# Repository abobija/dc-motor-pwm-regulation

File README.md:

# dc-motor-pwm-regulation
DC Motor PWM speed regulation and IR tachometer

## Description

One MCU is responsible for regulation speed of DC motor with Pulse Width Modulation (PWM), while other MCU have responsibility for measuring that speed. Everything will be easy if there is wire connection between this two MCUs, but there are no physical connection between them. CD which contains four drilled holes, rotates between IR emitting diode, and phototransistor on opposite side. When the hole drilled on CD comes to the sensor, and IR light pass from diode to transistor, internal MCU interrupt will be triggered. Applications for both MCUs are written in plain C.

## Demo

## Microcontrollers

- PWM Generator - `PIC12F628`
- Tachometer - `PIC16F886`

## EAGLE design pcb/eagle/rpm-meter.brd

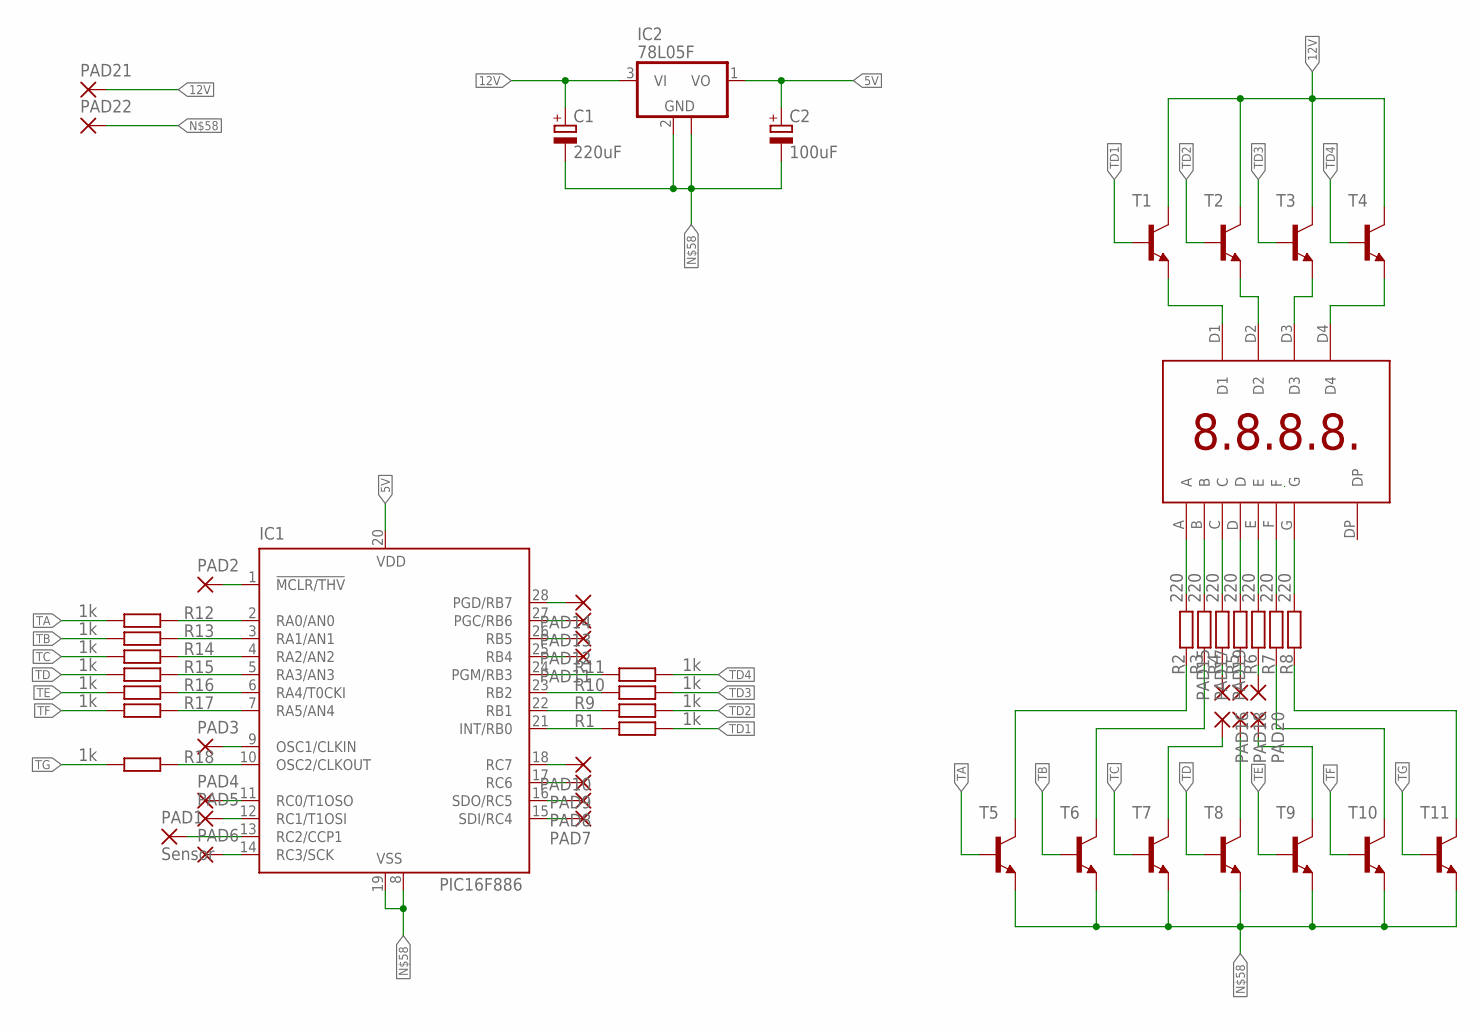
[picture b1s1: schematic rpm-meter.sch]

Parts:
C1: 220uF; E5-6
C2: 100uF; E5-5
IC1: PIC16F886; DIL28-3
IC2: 78L05F; SOT89
PAD1: Sensor; SMD2,54-5,08
PAD2, PAD3, PAD4, PAD5, PAD6, PAD7, PAD8, PAD9, PAD10, PAD11, PAD12, PAD13, PAD14: SMD2; SMD1,27-2,54
PAD15, PAD16, PAD17, PAD18, PAD19, PAD20: 2,54/0,8
PAD21, PAD22: SMD5; SMD2,54-5,08
R1, R9, R10, R11, R12, R13, R14, R15, R16, R17, R18: 1k; M0805
R2, R3, R4, R5, R6, R7, R8: 220; M0805
T1, T2, T3, T4, T5, T6, T7, T8, T9, T10, T11: -NPN-SOT23-EBC; SOT23-EBC
U$1: 4X7SEG-CA

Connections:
5V: C2.+, IC1.20 (VDD), IC2.1 (VO)
12V: C1.+, IC2.3 (VI), PAD21.1, T1.C, T2.C, T3.C, T4.C
unnamed: R2.2, U$1.A
unnamed: R3.2, U$1.B
unnamed: R4.2, U$1.C
unnamed: R5.2, U$1.D
unnamed: R6.2, U$1.E
unnamed: R7.2, U$1.F
unnamed: R8.2, U$1.G
unnamed: T2.E, U$1.D2
unnamed: T3.E, U$1.D3
unnamed: T1.E, U$1.D1
unnamed: T4.E, U$1.D4
unnamed: PAD17.1, R5.1
unnamed: PAD20.1, T9.C
unnamed: R7.1, T10.C
unnamed: R8.1, T11.C
unnamed: PAD16.1, T7.C
unnamed: R3.1, T6.C
unnamed: R2.1, T5.C
unnamed: IC1.21 (INT/RB0), R1.1
unnamed: IC1.22 (RB1), R9.1
unnamed: IC1.23 (RB2), R10.1
unnamed: IC1.24 (PGM/RB3), R11.1
unnamed: IC1.2 (RA0/AN0), R12.1
unnamed: IC1.3 (RA1/AN1), R13.1
unnamed: IC1.4 (RA2/AN2), R14.1
unnamed: IC1.5 (RA3/AN3), R15.1
unnamed: IC1.6 (RA4/T0CKI), R16.1
unnamed: IC1.7 (RA5/AN4), R17.1
unnamed: IC1.10 (OSC2/CLKOUT), R18.1
unnamed: IC1.13 (RC2/CCP1), PAD1.1
unnamed: IC1.1 (!MCLR/THV), PAD2.1
unnamed: IC1.9 (OSC1/CLKIN), PAD3.1
unnamed: IC1.11 (RC0/T1OSO), PAD4.1
unnamed: IC1.12 (RC1/T1OSI), PAD5.1
unnamed: IC1.14 (RC3/SCK), PAD6.1
unnamed: IC1.15 (SDI/RC4), PAD7.1
unnamed: IC1.16 (SDO/RC5), PAD8.1
unnamed: IC1.17 (RC6), PAD9.1
unnamed: IC1.18 (RC7), PAD10.1
unnamed: IC1.25 (RB4), PAD11.1
unnamed: IC1.26 (RB5), PAD12.1
unnamed: IC1.27 (PGC/RB6), PAD13.1
unnamed: IC1.28 (PGD/RB7), PAD14.1
unnamed: PAD15.1, R4.1
unnamed: PAD19.1, R6.1
unnamed: PAD18.1, T8.C
unnamed: C1.-, C2.-, IC1.8 (VSS), IC1.19 (VSS), IC2.2 (GND), IC2.2@1 (GND), PAD22.1, T5.E, T6.E, T7.E, T8.E, T9.E, T10.E, T11.E
TA: R12.2, T5.B
TB: R13.2, T6.B
TC: R14.2, T7.B
TD: R15.2, T8.B
TD1: R1.2, T1.B
TD2: R9.2, T2.B
TD3: R10.2, T3.B
TD4: R11.2, T4.B
TE: R16.2, T9.B
TF: R17.2, T10.B
TG: R18.2, T11.B

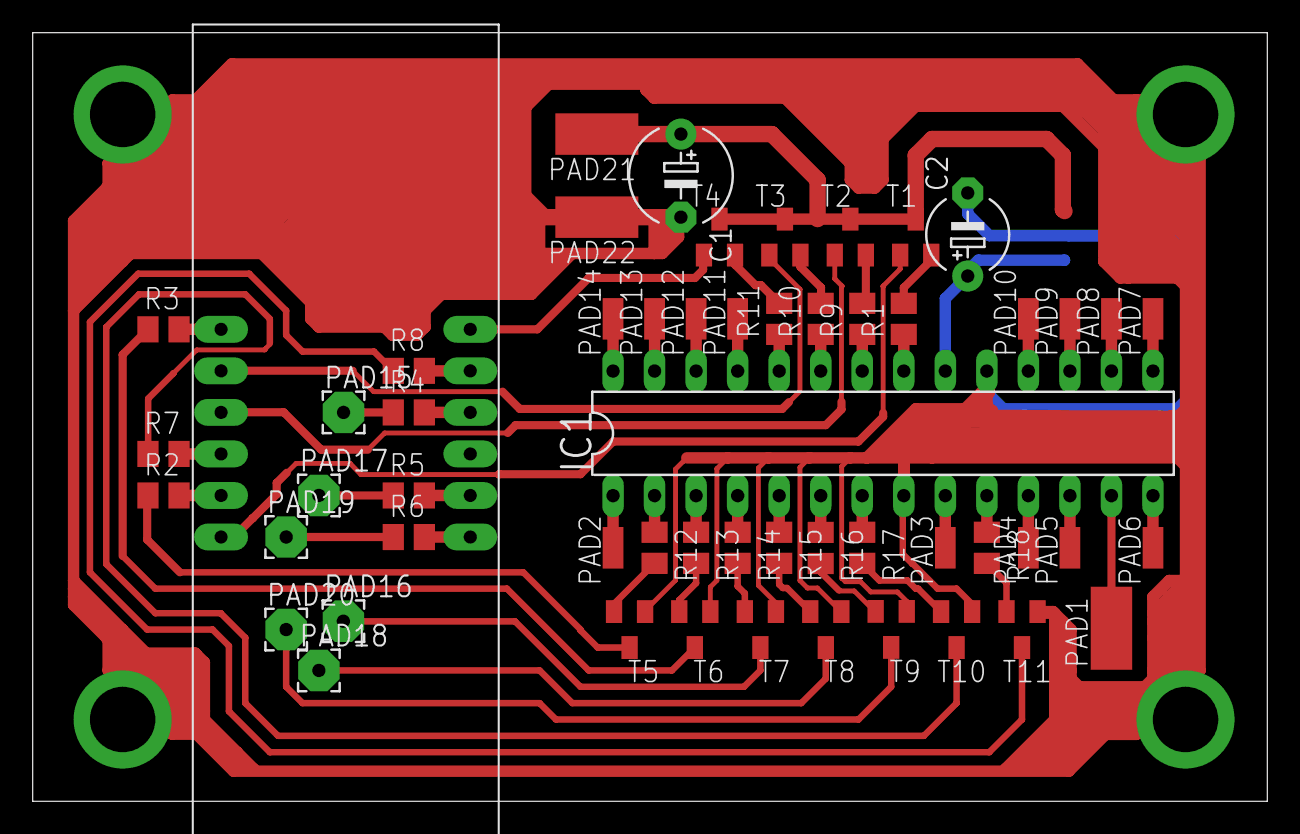
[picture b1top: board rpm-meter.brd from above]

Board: 2 copper layers, 75.5 x 47.0 mm, 56 parts (1 on the bottom side), 60 nets.

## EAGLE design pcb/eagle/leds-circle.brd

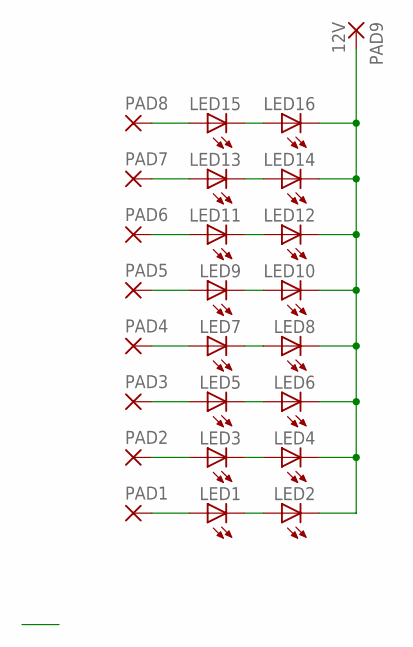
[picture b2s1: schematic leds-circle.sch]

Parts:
LED1, LED2, LED3, LED4, LED5, LED6, LED7, LED8, LED9, LED10, LED11, LED12, LED13, LED14, LED15, LED16: LED-FKIT-1206; FKIT-LED-1206
PAD1, PAD2, PAD3, PAD4, PAD5, PAD6, PAD7, PAD8: SMD2; SMD1,27-2,54
PAD9: 12V; SMD1,27-2,54

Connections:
unnamed: LED1.C, LED2.A
unnamed: LED3.C, LED4.A
unnamed: LED5.C, LED6.A
unnamed: LED7.C, LED8.A
unnamed: LED9.C, LED10.A
unnamed: LED11.C, LED12.A
unnamed: LED13.C, LED14.A
unnamed: LED15.C, LED16.A
unnamed: LED15.A, PAD8.1
unnamed: LED13.A, PAD7.1
unnamed: LED11.A, PAD6.1
unnamed: LED7.A, PAD4.1
unnamed: LED5.A, PAD3.1
unnamed: LED3.A, PAD2.1
unnamed: LED1.A, PAD1.1
unnamed: LED2.C, LED4.C, LED6.C, LED8.C, LED10.C, LED12.C, LED14.C, LED16.C, PAD9.1
unnamed: LED9.A, PAD5.1

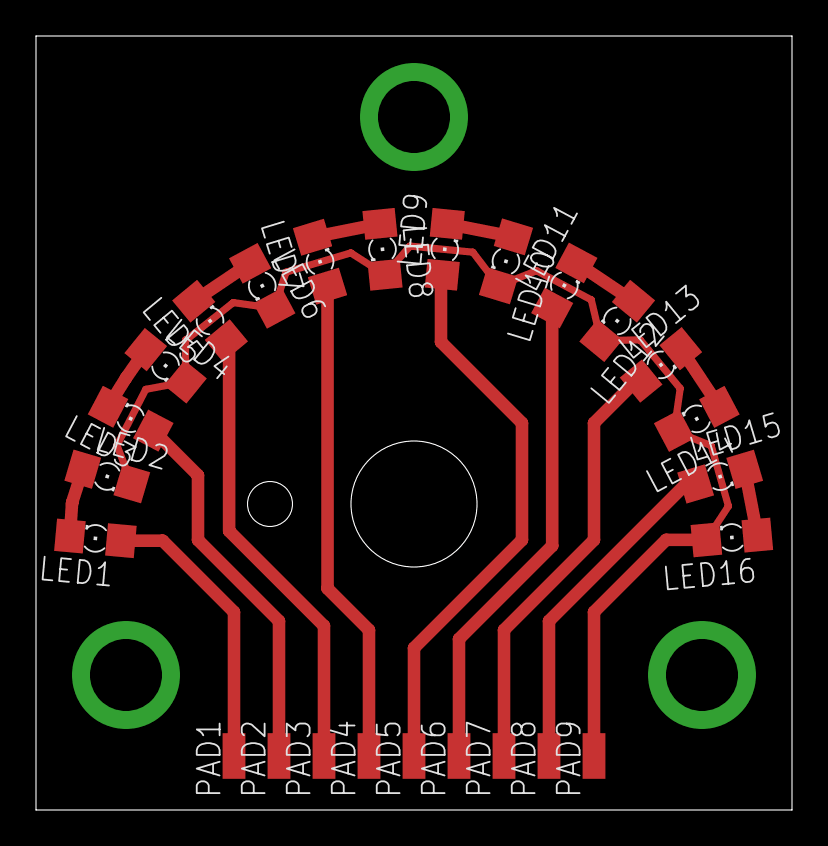
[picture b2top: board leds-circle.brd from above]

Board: 2 copper layers, 42.0 x 43.0 mm, 25 parts (0 on the bottom side), 17 nets.

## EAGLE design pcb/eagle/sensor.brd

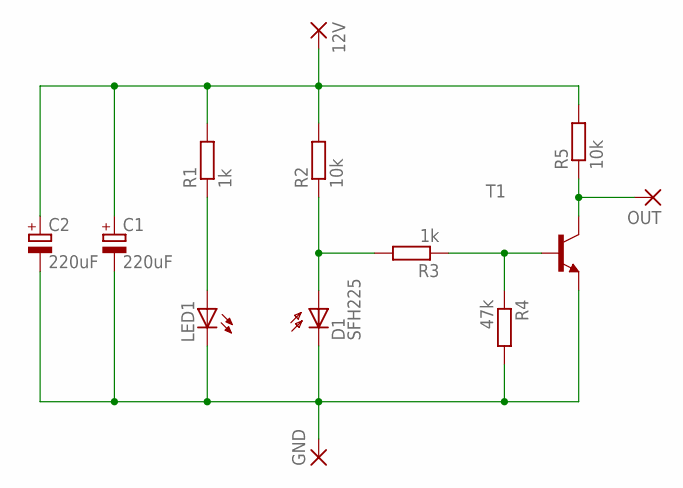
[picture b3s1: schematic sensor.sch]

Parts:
12V: SMD2; SMD1,27-2,54
C1, C2: 220uF; E5-6
D1: SFH225
GND: SMD2; SMD1,27-2,54
LED1: LED3MM
OUT: SMD2; SMD1,27-2,54
R1, R3: 1k; M0805
R2, R5: 10k; M0805
R4: 47k; M0805
T1: -NPN-SOT23-EBC; SOT23-EBC

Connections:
unnamed: C1.-, C2.-, D1.K (C), GND.1, LED1.K (C), R4.2, T1.E
unnamed: D1.A, R2.1, R3.2
unnamed: LED1.A, R1.1
unnamed: 12V.1, C1.+, C2.+, R1.2, R2.2, R5.2
unnamed: R3.1, R4.1, T1.B
unnamed: OUT.1, R5.1, T1.C

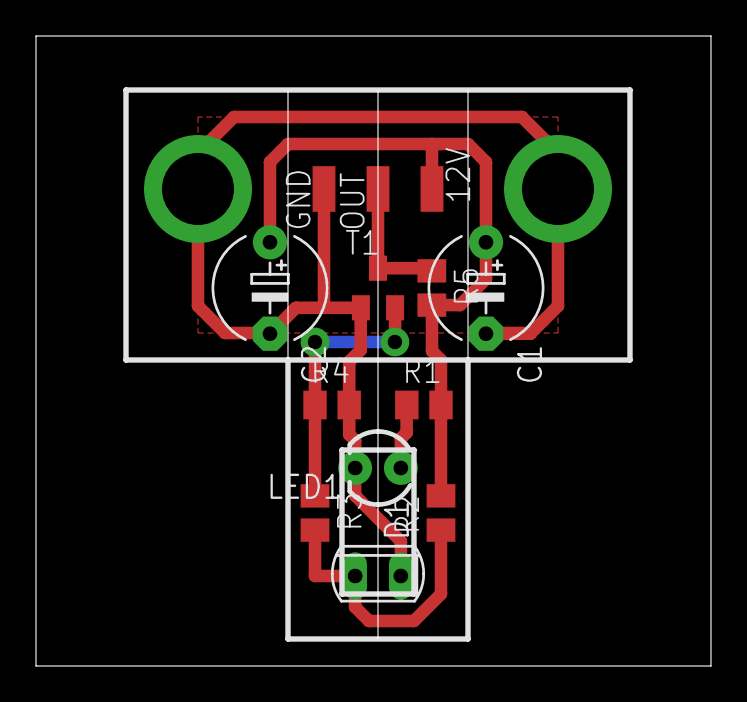
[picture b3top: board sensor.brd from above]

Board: 2 copper layers, 37.5 x 35.0 mm, 13 parts (0 on the bottom side), 6 nets.

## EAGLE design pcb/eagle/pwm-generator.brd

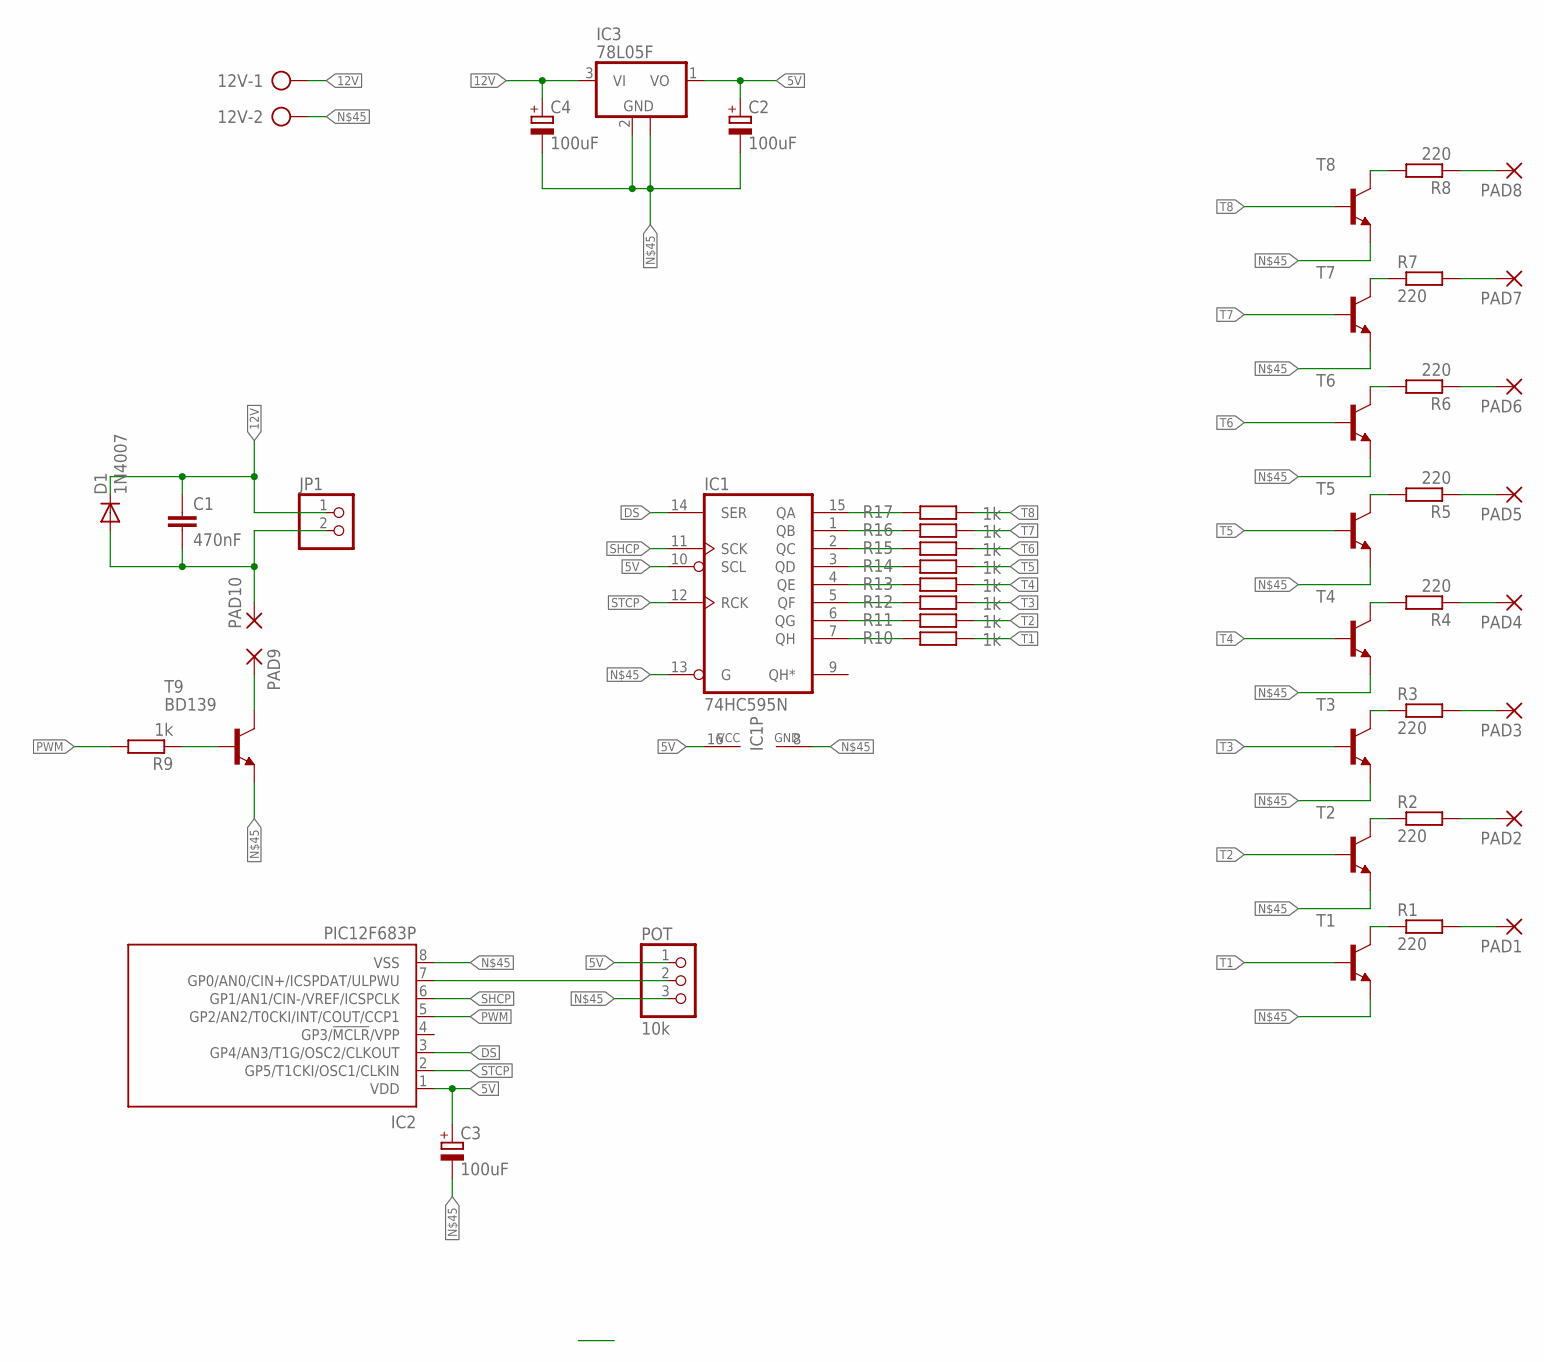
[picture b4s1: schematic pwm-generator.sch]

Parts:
12V: AK500/2
C1: 470nF; C025-025X050
C2, C4: 100uF; E2-5
C3: 100uF; E5-4
D1: 1N4007; DO35-7
IC1: 74HC595N; DIL16
IC2: PIC12F683P; DIL8
IC3: 78L05F; SOT89
JP1: PINHD-1X2; 1X02
PAD1, PAD2, PAD3, PAD4, PAD5, PAD6, PAD7, PAD8: SMD2; SMD1,27-2,54
PAD9, PAD10: 1,6/0,8
POT: 10k; 1X03
R1, R2, R3, R4, R5, R6, R7, R8: 220; M0805
R9, R10, R11, R12, R13, R14, R15, R16, R17: 1k; M0805
T1, T2, T3, T4, T5, T6, T7, T8: -NPN-SOT23-EBC; SOT23-EBC
T9: BD139; TO126

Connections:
5V: C2.+, C3.+, IC1.10 (SCL), IC1.16 (VCC), IC2.1 (VDD), IC3.1 (VO), POT.1
12V: 12V.1, C1.1, C4.+, D1.C, IC3.3 (VI), JP1.1
DS: IC1.14 (SER), IC2.3 (GP4/AN3/T1G/OSC2/CLKOUT)
unnamed: IC1.7 (QH), R10.2
unnamed: IC1.6 (QG), R11.2
unnamed: IC1.5 (QF), R12.2
unnamed: IC1.4 (QE), R13.2
unnamed: IC1.3 (QD), R14.2
unnamed: IC1.2 (QC), R15.2
unnamed: IC1.1 (QB), R16.2
unnamed: IC1.15 (QA), R17.2
unnamed: IC2.7 (GP0/AN0/CIN+/ICSPDAT/ULPWU), POT.2
unnamed: C1.2, D1.A, JP1.2, PAD10.1
unnamed: R9.1, T9.3 (B)
unnamed: R1.1, T1.C
unnamed: R2.1, T2.C
unnamed: R3.1, T3.C
unnamed: R4.2, T4.C
unnamed: R5.2, T5.C
unnamed: R6.2, T6.C
unnamed: R7.1, T7.C
unnamed: R8.2, T8.C
unnamed: PAD8.1, R8.1
unnamed: PAD7.1, R7.2
unnamed: PAD6.1, R6.1
unnamed: PAD5.1, R5.1
unnamed: PAD4.1, R4.1
unnamed: PAD3.1, R3.2
unnamed: PAD2.1, R2.2
unnamed: PAD1.1, R1.2
unnamed: PAD9.1, T9.2 (C)
unnamed: 12V.2, C2.-, C3.-, C4.-, IC1.8 (GND), IC1.13 (G), IC2.8 (VSS), IC3.2 (GND), IC3.2@1 (GND), POT.3, T1.E, T2.E, T3.E, T4.E, T5.E, T6.E, T7.E, T8.E, T9.1 (E)
PWM: IC2.5 (GP2/AN2/T0CKI/INT/COUT/CCP1), R9.2
SHCP: IC1.11 (SCK), IC2.6 (GP1/AN1/CIN-/VREF/ICSPCLK)
STCP: IC1.12 (RCK), IC2.2 (GP5/T1CKI/OSC1/CLKIN)
T1: R10.1, T1.B
T2: R11.1, T2.B
T3: R12.1, T3.B
T4: R13.1, T4.B
T5: R14.1, T5.B
T6: R15.1, T6.B
T7: R16.1, T7.B
T8: R17.1, T8.B

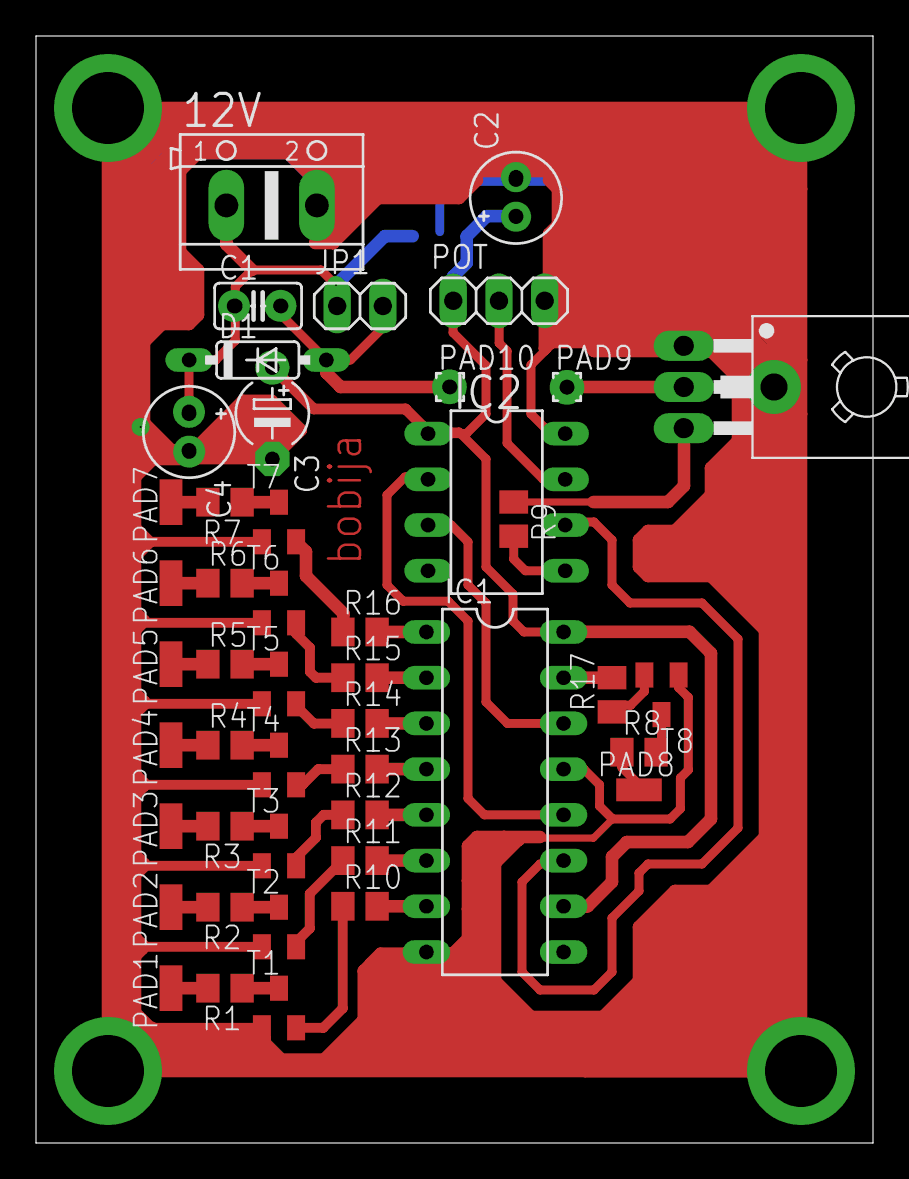
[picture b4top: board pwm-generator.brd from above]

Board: 2 copper layers, 46.5 x 61.5 mm, 47 parts (1 on the bottom side), 43 nets.

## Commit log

2019-07-10 Code, Simulation and PCBs
2019-07-21 Update README
    Added Description

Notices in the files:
parts and their libraries:
sparkfun-LED: Licensing: Creative Commons ShareAlike 4.0 International - https://creativecommons.org/licenses/by-sa/4.0
